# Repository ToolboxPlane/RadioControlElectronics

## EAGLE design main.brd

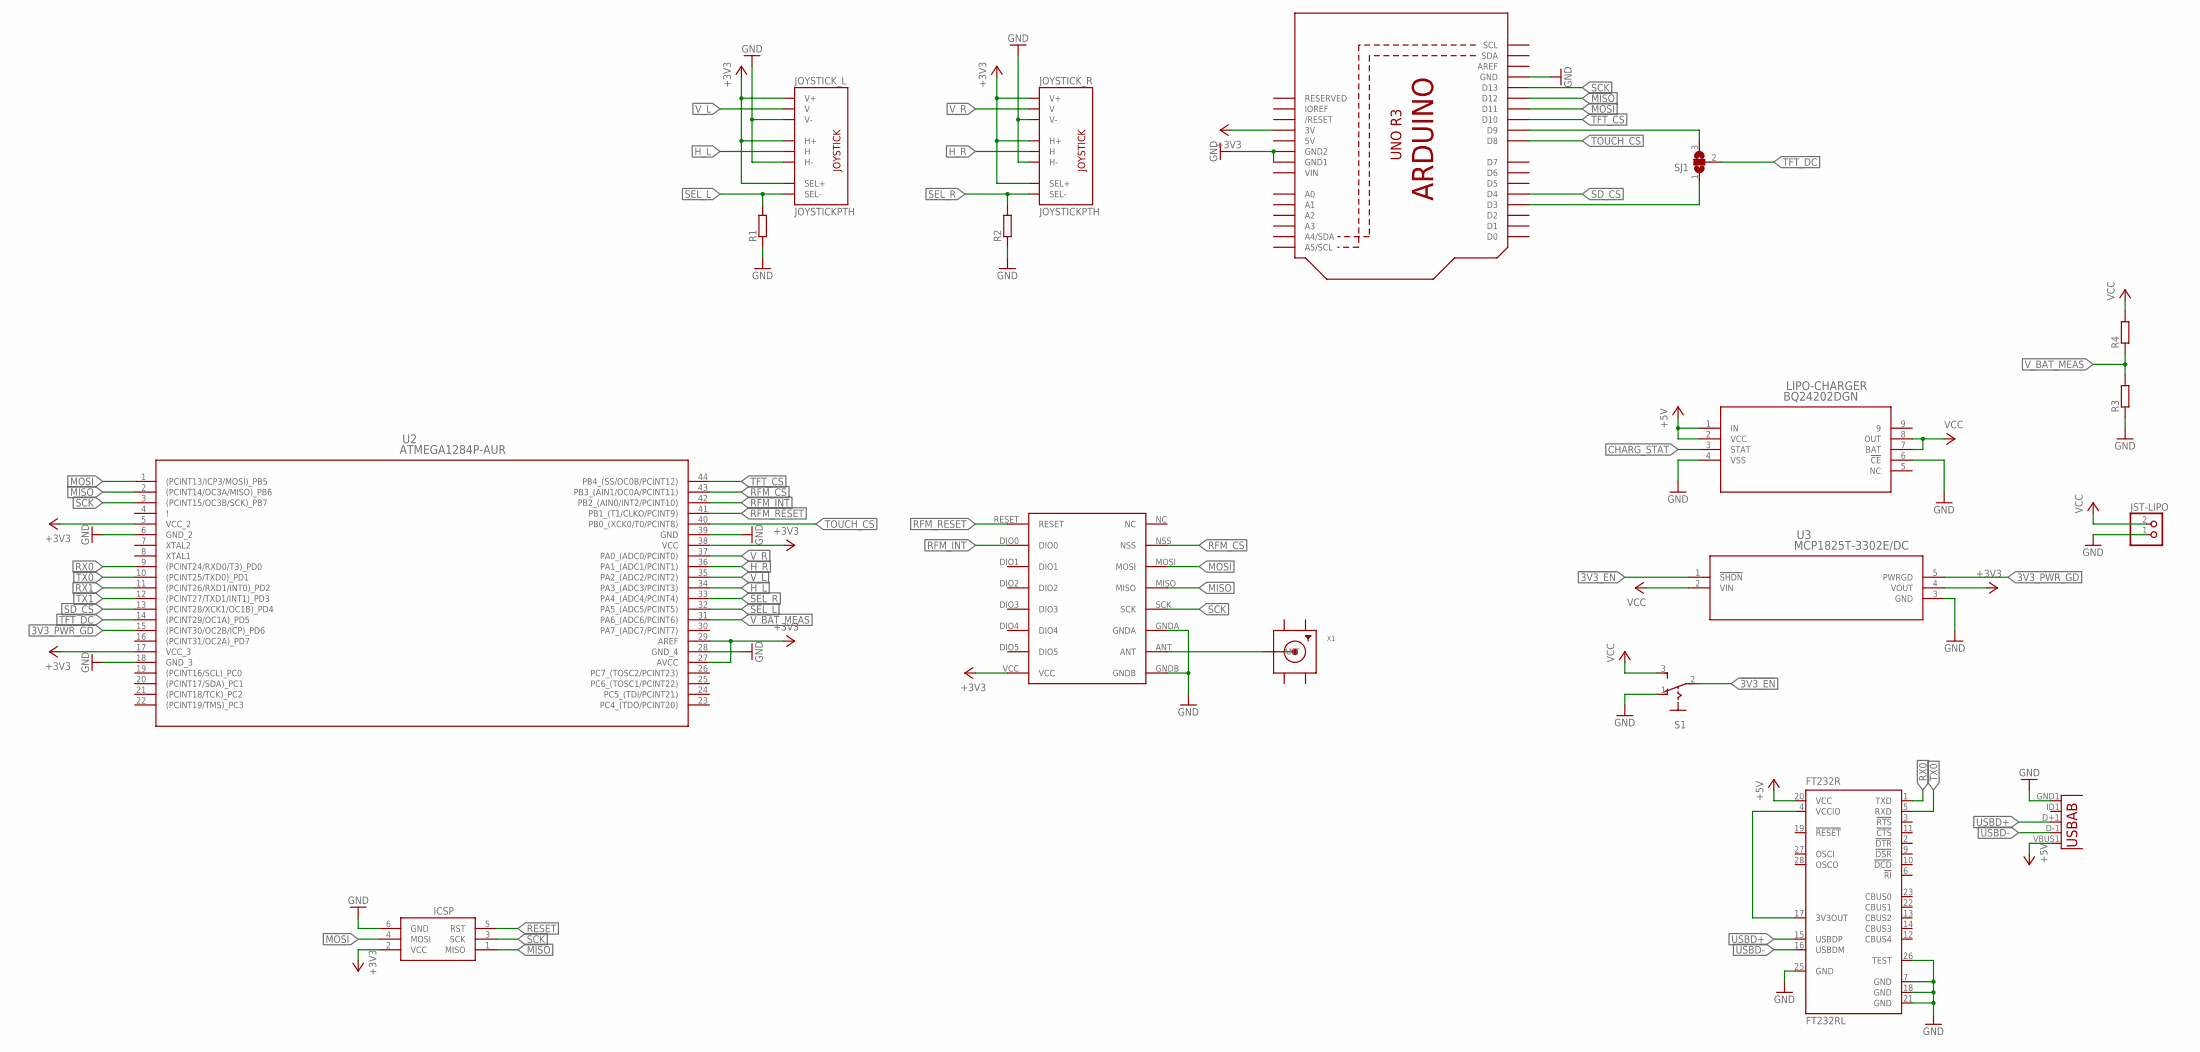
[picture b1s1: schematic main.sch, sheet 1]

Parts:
FT232R: FT232RL; SSOP28
ICSP: AVRISP-BOX
JOYSTICK_L: JOYSTICKPTH; JOYSTICK
JOYSTICK_R: JOYSTICKPTH; JOYSTICK
JST-LIPO: JST_2PIN-SMT-RA; JST-PH-2-SMT-RA
LCD: ARDUINOR3-DIMENSION; ARDUINOR3
LIPO-CHARGER: BQ24202DGN; DGN8
R1, R2, R3, R4: R-EU_R1206; R1206
RFM96W: RFM69HW; RFM
S1: 255SB
SJ1: SJ2W; SJ_2
U1: USB""; USB-MICRO-SMD
U2: ATMEGA1284P-AUR; 44A
U3: MCP1825T-3302E/DC; SOT-223_5MC
X1: SMACONNECTOR_EDGE; SMA_EDGELAUNCH

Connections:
3V3_PWR_GD: U2.15 ((PCINT30/OC2B/ICP)_PD6), U3.5 (PWRGD)
5V: LCD.5V
!3V3_EN: S1.2, U3.1 (!SHDN)
+3V3: ICSP.2 (VCC), JOYSTICK_L.B1A (SEL+), JOYSTICK_L.H1 (H+), JOYSTICK_L.V1 (V+), JOYSTICK_R.B1A (SEL+), JOYSTICK_R.H1 (H+), JOYSTICK_R.V1 (V+), LCD.3V, RFM96W.VCC, U2.5 (VCC_2), U2.17 (VCC_3), U2.27 (AVCC), U2.29 (AREF), U2.38 (VCC), U3.4 (VOUT)
+5V: FT232R.20 (VCC), LIPO-CHARGER.1 (IN), LIPO-CHARGER.2 (VCC), U1.VBUS1 (VBUS)
CHARG_STAT: LIPO-CHARGER.3 (STAT)
GND: FT232R.7 (GND), FT232R.18 (GND), FT232R.21 (GND), FT232R.25 (GND), FT232R.26 (TEST), ICSP.6 (GND), JOYSTICK_L.H3 (H-), JOYSTICK_L.V3 (V-), JOYSTICK_R.H3 (H-), JOYSTICK_R.V3 (V-), JST-LIPO.1 (2), LCD.GND, LCD.GND1, LCD.GND2, LIPO-CHARGER.4 (VSS), LIPO-CHARGER.6 (!CE), R1.1, R2.1, R3.1, RFM96W.GNDA, RFM96W.GNDB, S1.1 (O), U1.GND1 (GND), U2.6 (GND_2), U2.18 (GND_3), U2.28 (GND_4), U2.39 (GND), U3.3 (GND)
GND1: X1.GND@4 (GND1)
GND2: X1.GND@3 (GND2)
GND3: X1.GND@2 (GND3)
GND4: X1.GND@1 (GND4)
H_L: JOYSTICK_L.H2 (H), U2.34 (PA3_(ADC3/PCINT3))
H_R: JOYSTICK_R.H2 (H), U2.36 (PA1_(ADC1/PCINT1))
MISO: ICSP.1 (MISO), LCD.D12, RFM96W.MISO, U2.2 ((PCINT14/OC3A/MISO)_PB6)
MOSI: ICSP.4 (MOSI), LCD.D11, RFM96W.MOSI, U2.1 ((PCINT13/ICP3/MOSI)_PB5)
unnamed: RFM96W.ANT, X1.P (ANT)
unnamed: FT232R.4 (VCCIO), FT232R.17 (3V3OUT)
unnamed: LCD.D9, SJ1.3
RESET: ICSP.5 (RST)
RFM_CS: RFM96W.NSS, U2.43 (PB3_(AIN1/OC0A/PCINT11))
RFM_INT: RFM96W.DIO0, U2.42 (PB2_(AIN0/INT2/PCINT10))
RFM_RESET: RFM96W.RESET, U2.41 (PB1_(T1/CLKO/PCINT9))
RX0: FT232R.1 (TXD), U2.9 ((PCINT24/RXD0/T3)_PD0)
RX1: U2.11 ((PCINT26/RXD1/INT0)_PD2)
SCK: ICSP.3 (SCK), LCD.D13, RFM96W.SCK, U2.3 ((PCINT15/OC3B/SCK)_PB7)
SD_CS: LCD.D4, U2.13 ((PCINT28/XCK1/OC1B)_PD4)
SEL_L: JOYSTICK_L.B2A (SEL-), R1.2, U2.32 (PA5_(ADC5/PCINT5))
SEL_R: JOYSTICK_R.B2A (SEL-), R2.2, U2.33 (PA4_(ADC4/PCINT4))
TFT_CS: LCD.D10, U2.44 (PB4_(SS/OC0B/PCINT12))
TFT_DC: SJ1.2, U2.14 ((PCINT29/OC1A)_PD5)
TFT_DC_MODIFIED: LCD.D3, SJ1.1
TOUCH_CS: LCD.D8, U2.40 (PB0_(XCK0/T0/PCINT8))
TX0: FT232R.5 (RXD), U2.10 ((PCINT25/TXD0)_PD1)
TX1: U2.12 ((PCINT27/TXD1/INT1)_PD3)
USBD+: FT232R.15 (USBDP), U1.D+1 (D+)
USBD-: FT232R.16 (USBDM), U1.D-1 (D-)
VCC: JST-LIPO.2 (1), LIPO-CHARGER.7 (BAT), LIPO-CHARGER.8 (OUT), R4.2, S1.3 (S), U3.2 (VIN)
VIN: LCD.VIN
V_BAT_MEAS: R3.2, R4.1, U2.31 (PA6_(ADC6/PCINT6))
V_L: JOYSTICK_L.V2 (V), U2.35 (PA2_(ADC2/PCINT2))
V_R: JOYSTICK_R.V2 (V), U2.37 (PA0_(ADC0/PCINT0))

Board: 2 copper layers, 18 parts (0 on the bottom side), 31 nets, no tracks yet.
